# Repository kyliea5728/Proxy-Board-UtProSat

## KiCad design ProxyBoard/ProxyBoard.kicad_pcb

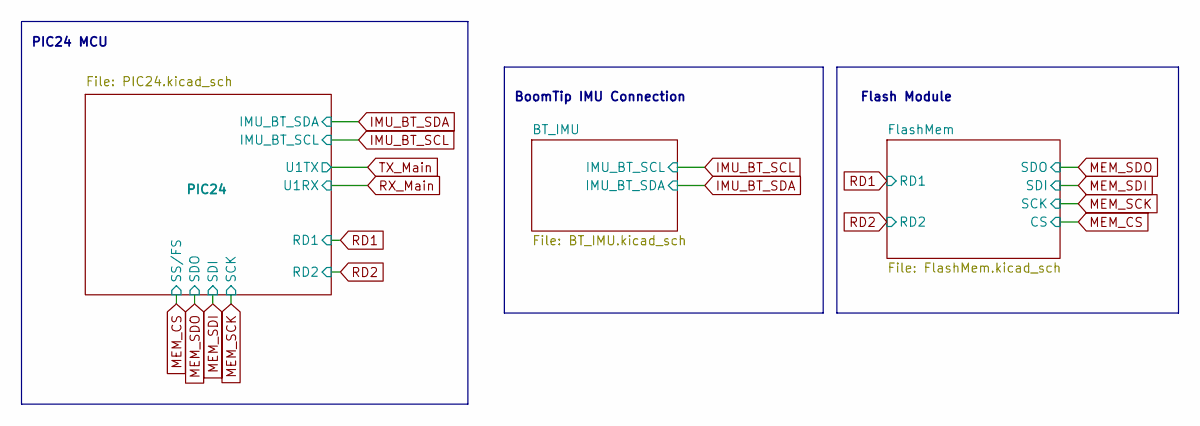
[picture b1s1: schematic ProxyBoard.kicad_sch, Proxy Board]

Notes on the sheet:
BoomTip IMU Connection
Flash Module
PIC24 MCU

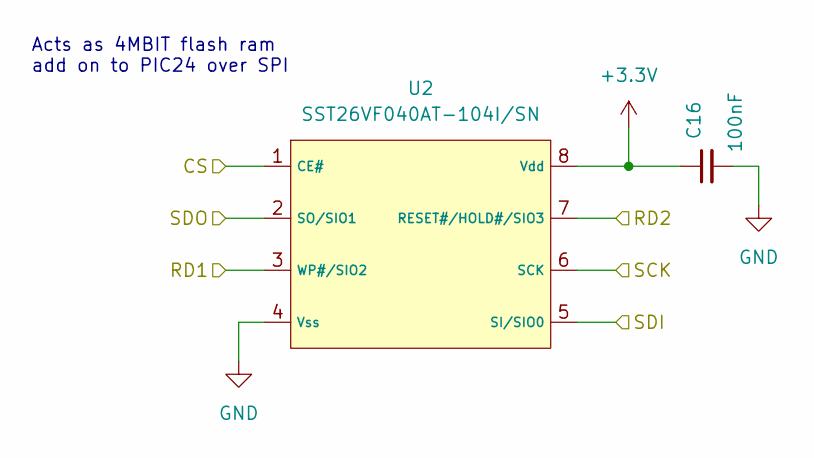
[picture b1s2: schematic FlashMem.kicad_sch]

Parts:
C16: 100nF; C_0603_1608Metric
U2: SST26VF040AT-104I/SN; SOIC-8W_5.3x5.3mm_P1.27mm

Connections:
+3V3: C16.1, U2.8 (Vdd); also elsewhere on the board
GND: C16.2, U2.4 (Vss); also elsewhere on the board
MEM_CS: U2.1 (CE#); also elsewhere on the board
MEM_SCK: U2.6 (SCK); also elsewhere on the board
MEM_SDI: U2.5 (SI/SIO0); also elsewhere on the board
MEM_SDO: U2.2 (SO/SIO1); also elsewhere on the board
RD1: U2.3 (WP#/SIO2); also elsewhere on the board
RD2: U2.7 (RESET#/HOLD#/SIO3); also elsewhere on the board

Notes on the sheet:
Acts as 4MBIT flash ram add on to PIC24 over SPI

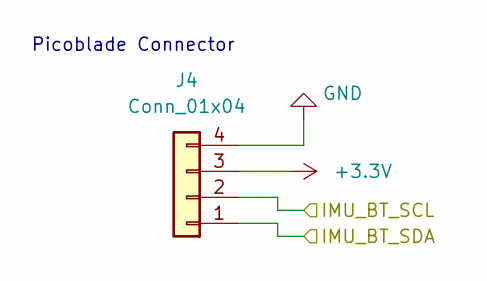
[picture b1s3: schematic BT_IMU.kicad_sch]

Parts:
J4: Conn_01x04; MOLEX_533980471

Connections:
+3V3: J4.3; also elsewhere on the board
GND: J4.4; also elsewhere on the board
IMU_BT_SCL: J4.2; also elsewhere on the board
IMU_BT_SDA: J4.1; also elsewhere on the board

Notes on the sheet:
Picoblade Connector

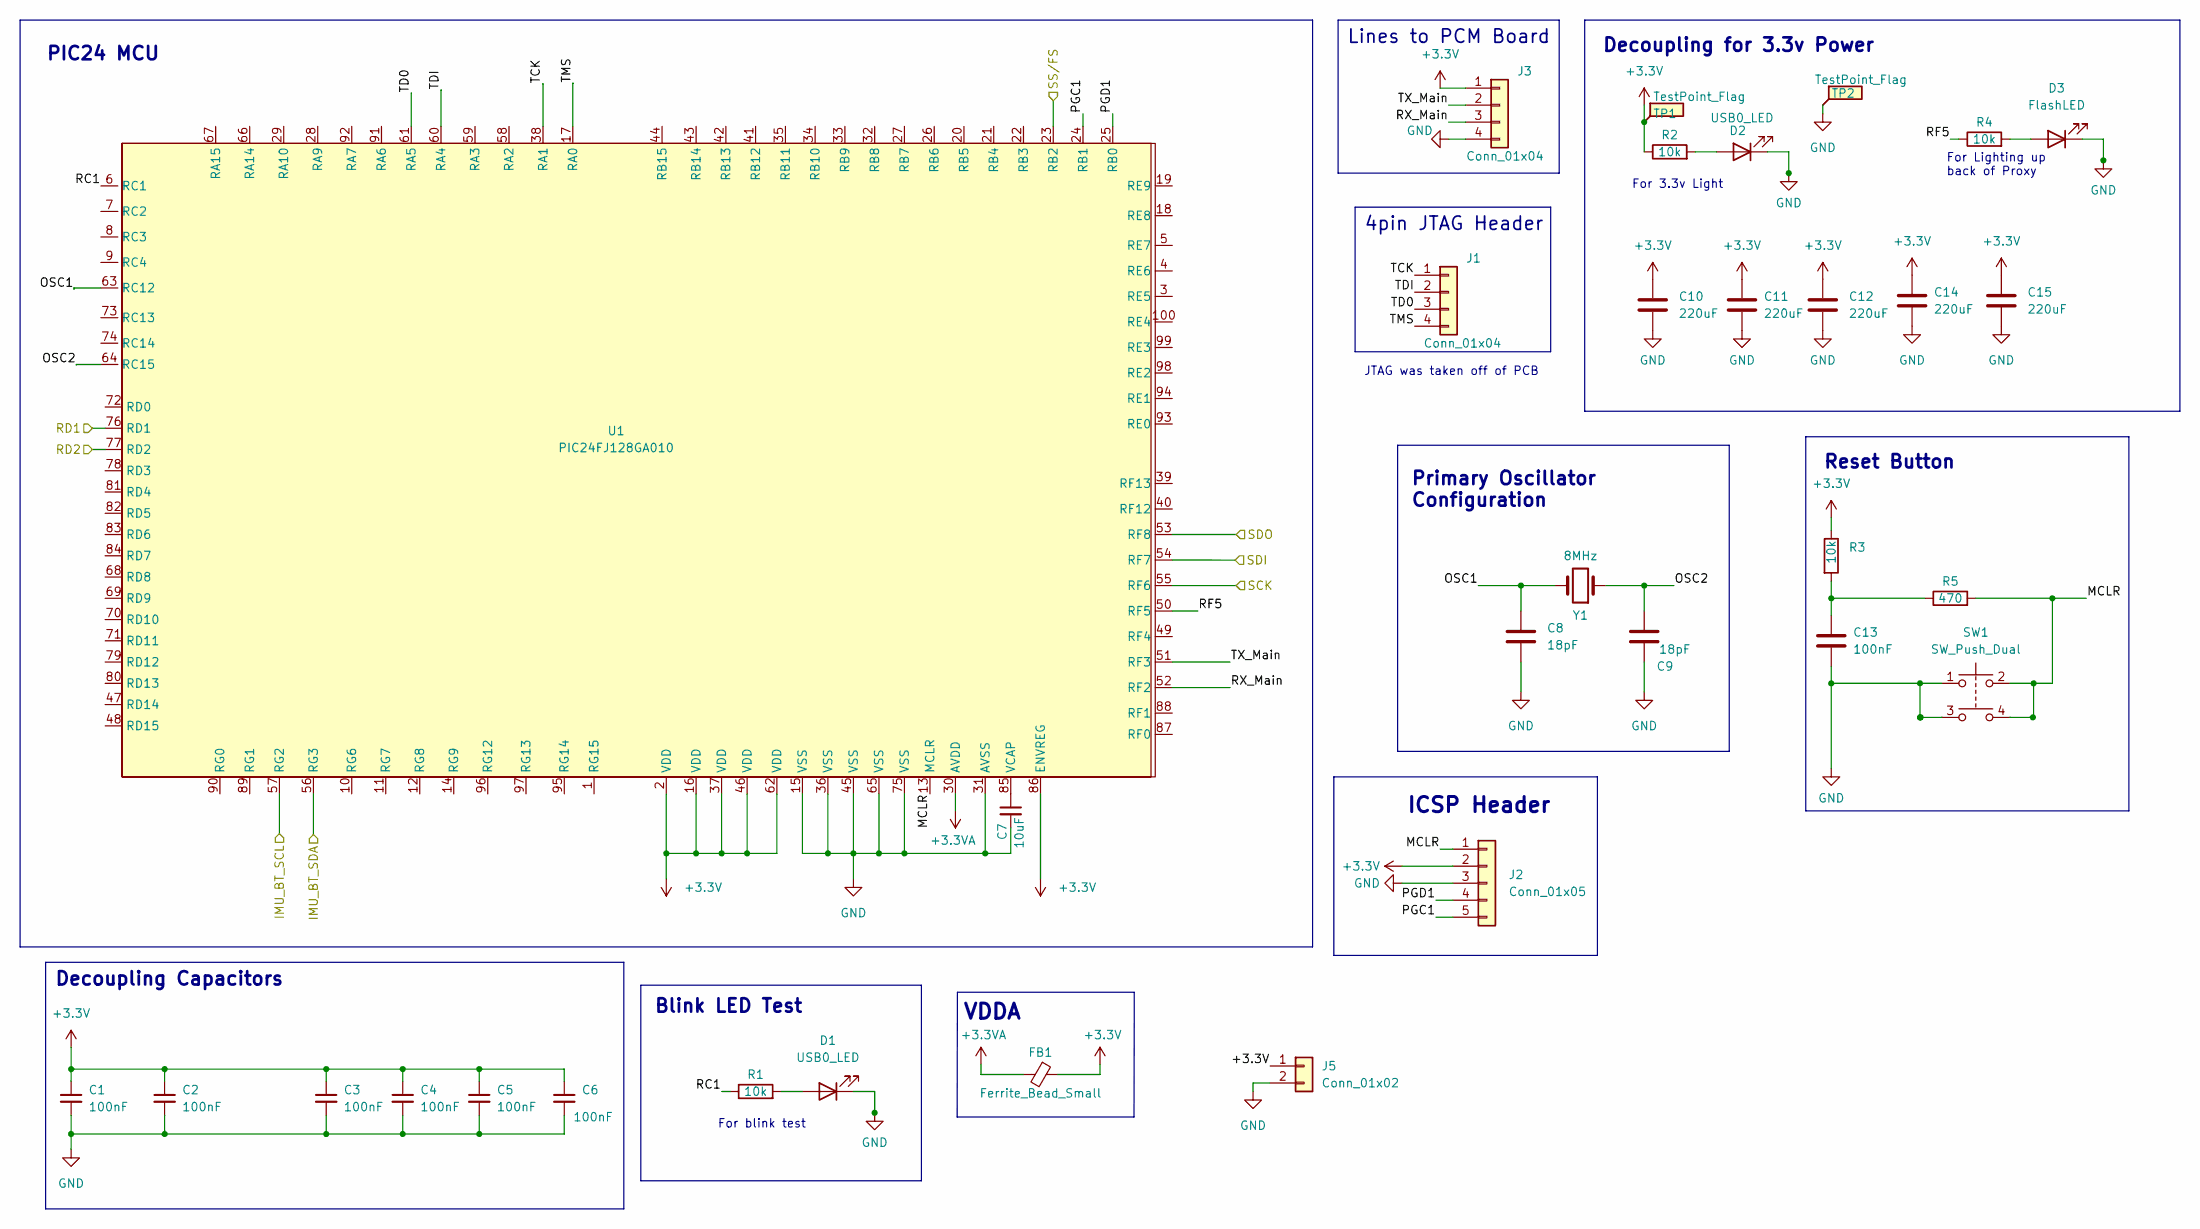
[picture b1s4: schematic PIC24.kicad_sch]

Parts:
C1, C2, C3, C4, C5, C6, C13: 100nF; C_0603_1608Metric
C7: 10uF; C_0603_1608Metric
C8, C9: 18pF; C_0603_1608Metric
C10, C11, C12, C14, C15: 220uF; C_1210_3225Metric
D1, D2: USB0_LED; D_0603_1608Metric
D3: FlashLED; D_0603_1608Metric
FB1: Ferrite_Bead_Small; L_0805_2012Metric; MPN ILBB0805ER121V
J1: Conn_01x04; PinHeader_1x04_P2.54mm_Vertical
J2: Conn_01x05; PinHeader_1x05_P2.54mm_Vertical
J3: Conn_01x04; MOLEX_533980471
J5: Conn_01x02; PinHeader_1x02_P2.54mm_Vertical
R1, R2, R3, R4: 10k; R_0603_1608Metric
R5: 470; R_0603_1608Metric
SW1: SW_Push_Dual; SW_B3F-1000
TP1, TP2: TestPoint_Flag; TESTPOINT_5017
U1: PIC24FJ128GA010; QFP40P1400X1400X120-100N
Y1: 8MHz; Crystal_SMD_Abracon_ABM3-2Pin_5.0x3.2mm

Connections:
+3.3VA: FB1.2, U1.30 (AVDD)
+3V3: C1.1, C2.1, C3.1, C4.1, C5.1, C6.1, C10.1, C11.1, C12.1, C14.1, C15.1, FB1.1, J2.2, J3.1, R2.1, R3.1, TP1.1, U1.2 (VDD), U1.16 (VDD), U1.37 (VDD), U1.46 (VDD), U1.62 (VDD), U1.86 (ENVREG); also elsewhere on the board
/PIC24/+3.3V: J5.1
/PIC24/MCLR: J2.1, R5.2, SW1.2, SW1.4, U1.13 (MCLR)
/PIC24/OSC1: C8.2, U1.63 (RC12), Y1.2
/PIC24/OSC2: C9.2, U1.64 (RC15), Y1.1
/PIC24/PGC1: J2.5, U1.24 (RB1)
/PIC24/PGD1: J2.4, U1.25 (RB0)
/PIC24/RC1: R1.1, U1.6 (RC1)
/PIC24/RF5: R4.1, U1.50 (RF5)
/PIC24/RX_Main: J3.3, U1.52 (RF2)
/PIC24/TCK: J1.1, U1.38 (RA1)
/PIC24/TD0: J1.3, U1.61 (RA5)
/PIC24/TDI: J1.2, U1.60 (RA4)
/PIC24/TMS: J1.4, U1.17 (RA0)
/PIC24/TX_Main: J3.2, U1.51 (RF3)
GND: C1.2, C2.2, C3.2, C4.2, C5.2, C6.2, C7.2, C8.1, C9.1, C10.2, C11.2, C12.2, C13.2, C14.2, C15.2, D1.1 (K), D2.1 (K), D3.1 (K), J2.3, J3.4, J5.2, SW1.1, SW1.3, TP2.1, U1.15 (VSS), U1.31 (AVSS), U1.36 (VSS), U1.45 (VSS), U1.65 (VSS), U1.75 (VSS); also elsewhere on the board
IMU_BT_SCL: U1.57 (RG2); also elsewhere on the board
IMU_BT_SDA: U1.56 (RG3); also elsewhere on the board
MEM_CS: U1.23 (RB2); also elsewhere on the board
MEM_SCK: U1.55 (RF6); also elsewhere on the board
MEM_SDI: U1.54 (RF7); also elsewhere on the board
MEM_SDO: U1.53 (RF8); also elsewhere on the board
unnamed: C7.1, U1.85 (VCAP)
unnamed: C13.1, R3.2, R5.1
unnamed: D1.2 (A), R1.2
unnamed: D2.2 (A), R2.2
unnamed: D3.2 (A), R4.2
RD1: U1.76 (RD1); also elsewhere on the board
RD2: U1.77 (RD2); also elsewhere on the board

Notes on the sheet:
4pin JTAG Header
PIC24 MCU
For 3.3v Light
ICSP Header
Primary Oscillator Configuration
VDDA
JTAG was taken off of PCB
For Lighting up back of Proxy
For blink test
Lines to PCM Board
Decoupling Capacitors
Reset Button
Blink LED Test
Decoupling for 3.3v Power

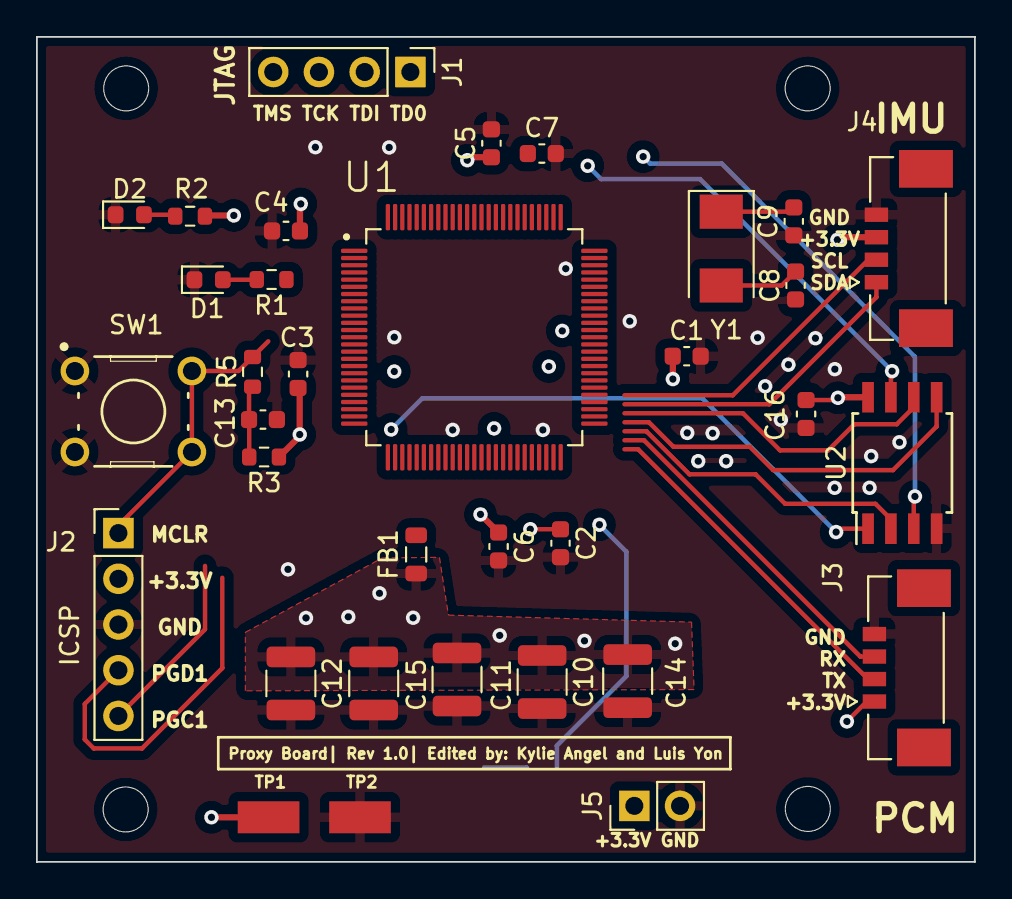
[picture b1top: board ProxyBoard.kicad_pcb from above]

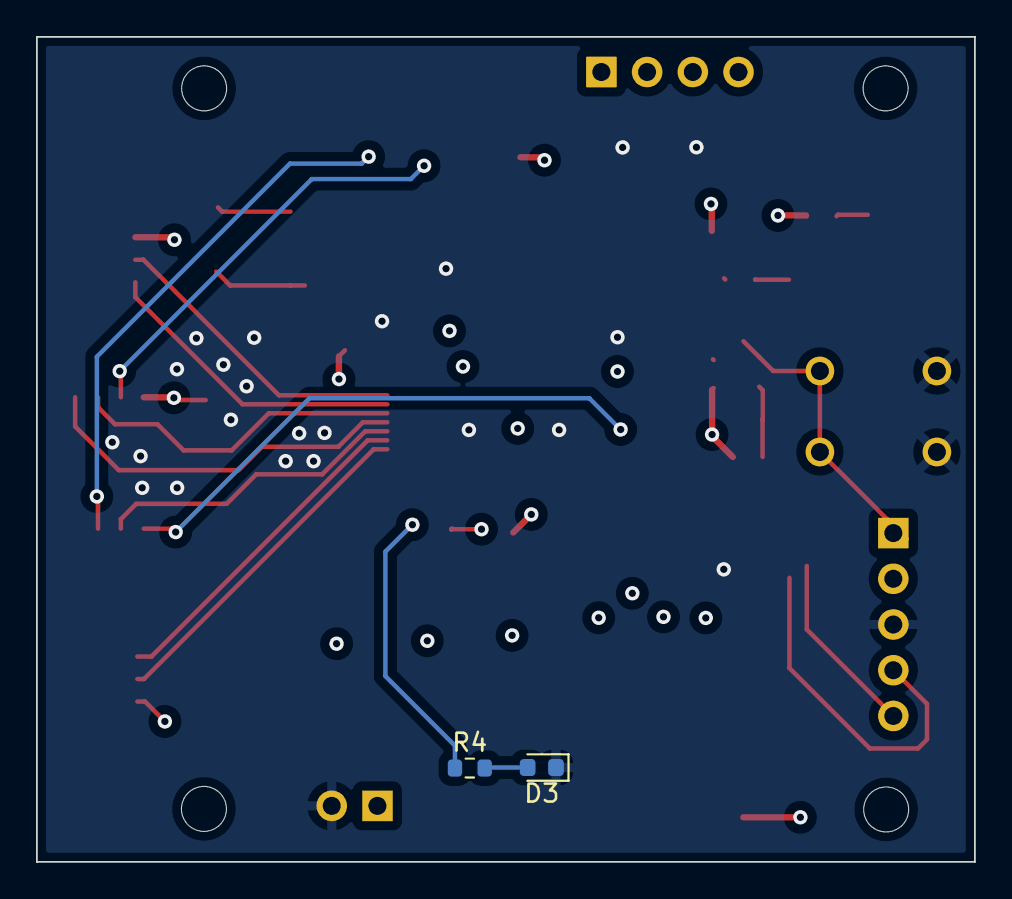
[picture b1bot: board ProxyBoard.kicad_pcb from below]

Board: 4 copper layers, 52.1 x 45.8 mm, 36 parts (2 on the bottom side), 29 nets.
